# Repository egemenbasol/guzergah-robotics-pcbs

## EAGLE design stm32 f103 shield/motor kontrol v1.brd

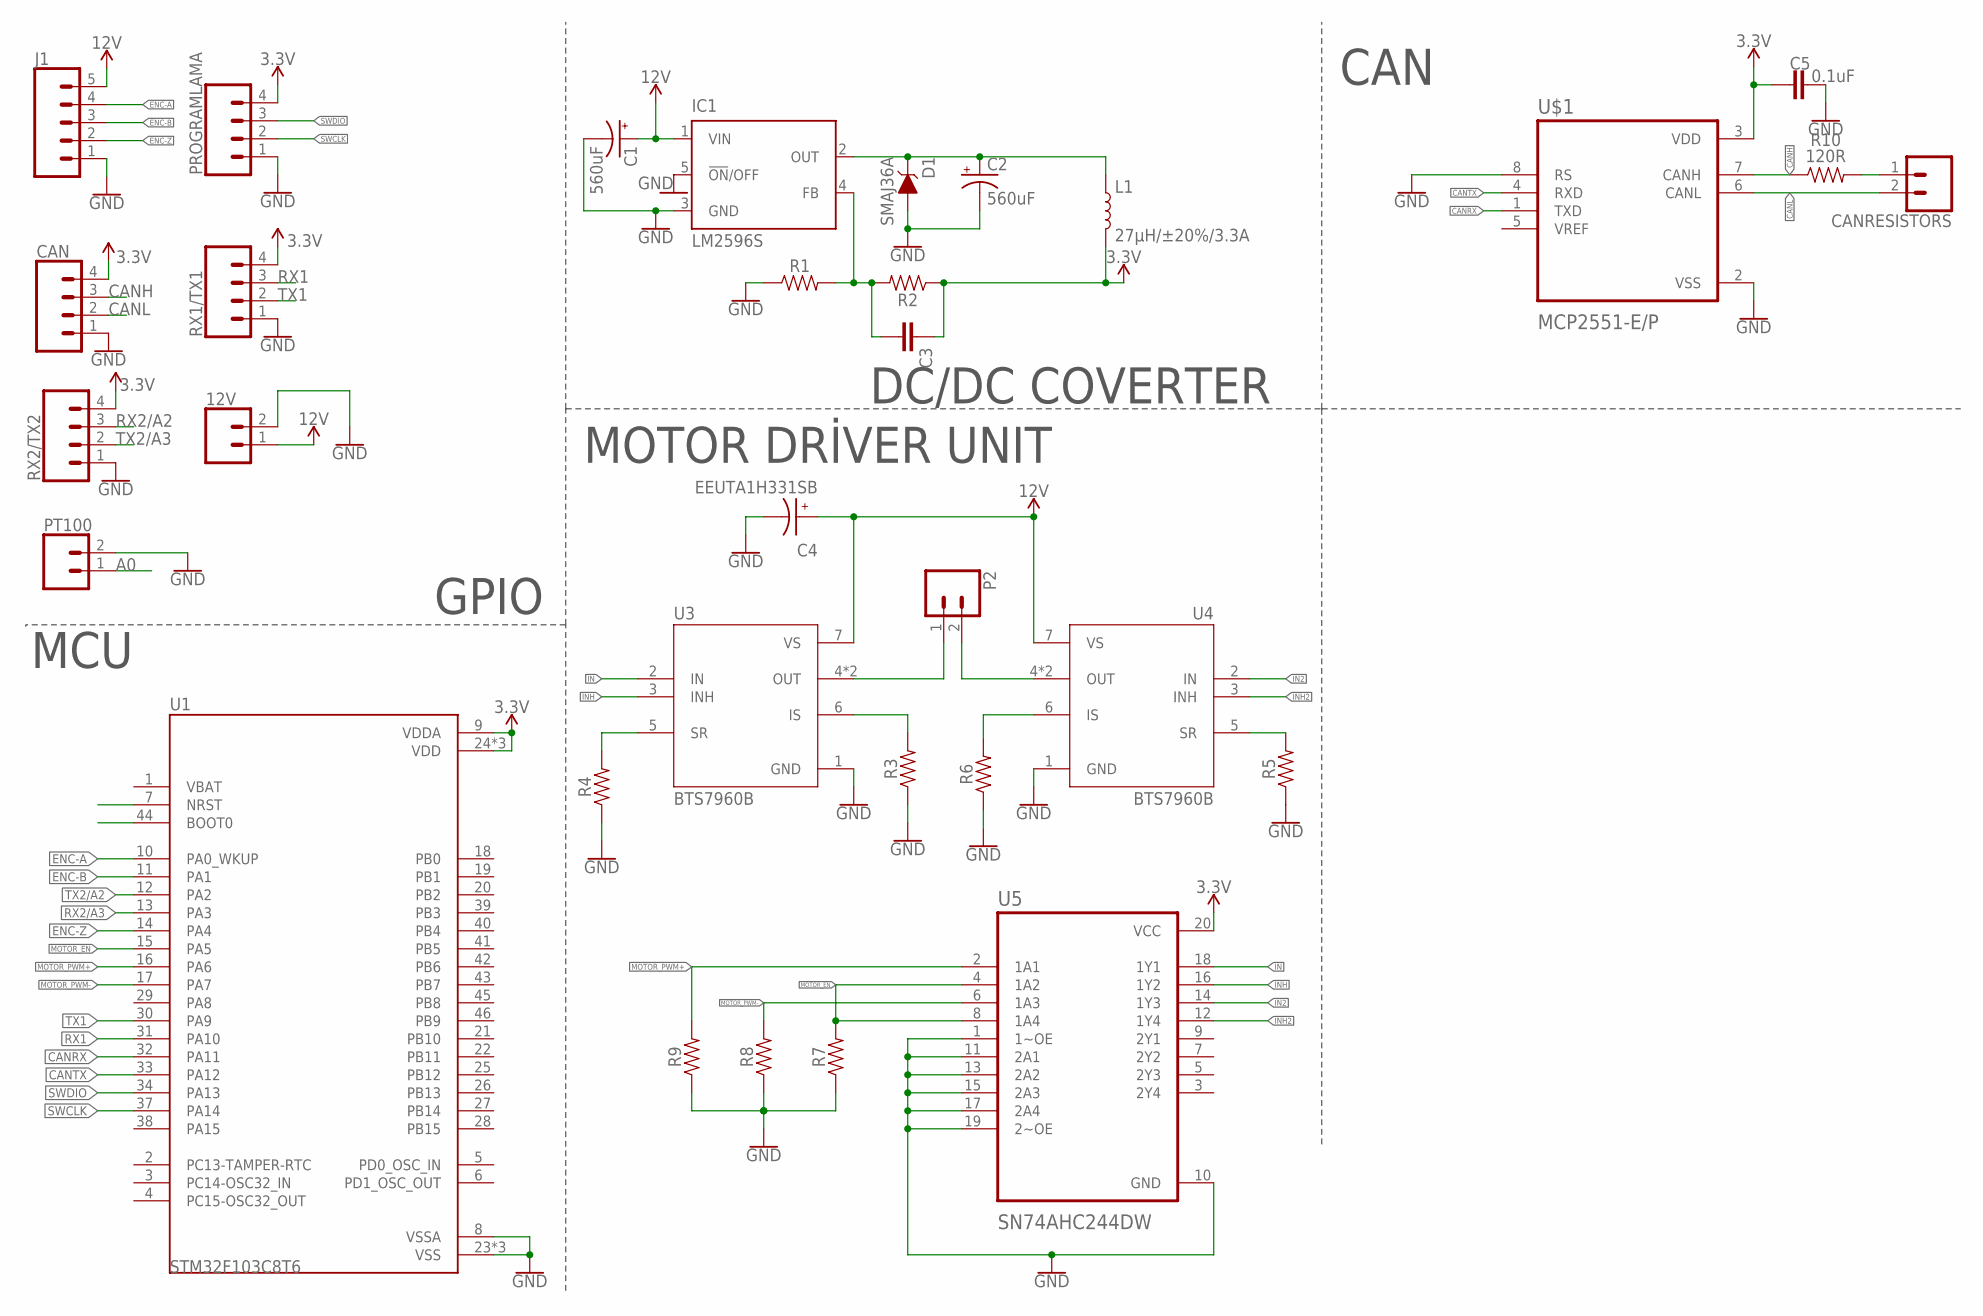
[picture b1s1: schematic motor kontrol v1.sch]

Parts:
12V: CONN_023.5MM_LOCK; SCREWTERMINAL-3.5MM-2_LOCK
C1, C2: 560uF; PANASONIC_G
C3: CAP-0805; 0805
C4: EEUTA1H331SB; CAPPRD750W80D1600H1500
C5: 0.1uF; 0805
CAN: CONN_04SCREW_LOCK; SCREWTERMINAL-3.5MM-4_LOCK
CANRESISTORS: CONN_02LOCK_LONGPADS; 1X02_LOCK_LONGPADS
D1: SMAJ36A; DO-214AC
IC1: LM2596S; TO263-5
J1: CONN_05SCREW; SCREWTERMINAL-3.5MM-5
L1: 27µH/±20%/3.3A; INDUCTOR_SDR1307
P2: CONN_023.5MM_LOCK; SCREWTERMINAL-3.5MM-2_LOCK
PROGRAMLAMA: CONN_04SCREW_LOCK; SCREWTERMINAL-3.5MM-4_LOCK
PT100: CONN_023.5MM_LOCK; SCREWTERMINAL-3.5MM-2_LOCK
R1, R2, R3, R4, R5, R6, R7, R8, R9: 0805
R10: 120R; 0805
RX1/TX1, RX2/TX2: CONN_04SCREW_LOCK; SCREWTERMINAL-3.5MM-4_LOCK
U1: STM32F103C8T6; QFP50P900X900X160-48N
U3, U4: BTS7960B; DPAK127P1490X440-8N
U5: SN74AHC244DW; SOIC127P1030X265-20N
U$1: MCP2551-E/P; DIP787W46P254L927H533Q8

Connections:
3.3V: C3.1, C5.2, CAN.4, L1.P$2 (2), PROGRAMLAMA.4, R2.1, RX1/TX1.4, RX2/TX2.4, U1.9 (VDDA), U1.24 (VDD), U1.36 (VDD), U1.48 (VDD), U5.20 (VCC), U$1.3 (VDD)
12V: 12V.1, C1.+, C4.P, IC1.1 (VIN), J1.5, U3.7 (VS), U4.7 (VS)
A0: PT100.1
CANH: CAN.3, R10.1, U$1.7 (CANH)
CANL: CAN.2, CANRESISTORS.2, U$1.6 (CANL)
CANRX: U1.32 (PA11), U$1.1 (TXD)
CANTX: U1.33 (PA12), U$1.4 (RXD)
ENC-A: J1.4, U1.10 (PA0_WKUP)
ENC-B: J1.3, U1.11 (PA1)
ENC-Z: J1.2, U1.14 (PA4)
GND: 12V.2, C1.-, C2.-, C4.N, C5.1, CAN.1, D1.A, IC1.3 (GND), IC1.5 (!ON!/OFF), J1.1, PROGRAMLAMA.1, PT100.2, R1.1, R3.1, R4.1, R5.1, R6.1, R7.1, R8.1, R9.1, RX1/TX1.1, RX2/TX2.1, U1.8 (VSSA), U1.23 (VSS), U1.35 (VSS), U1.47 (VSS), U3.1 (GND), U4.1 (GND), U5.1 (1~OE), U5.10 (GND), U5.11 (2A1), U5.13 (2A2), U5.15 (2A3), U5.17 (2A4), U5.19 (2~OE), U$1.2 (VSS), U$1.8 (RS)
IN: U3.2 (IN), U5.18 (1Y1)
IN2: U4.2 (IN), U5.14 (1Y3)
INH: U3.3 (INH), U5.16 (1Y2)
INH2: U4.3 (INH), U5.12 (1Y4)
MOTOR_EN: R7.2, U1.15 (PA5), U5.4 (1A2), U5.8 (1A4)
MOTOR_PWM+: R9.2, U1.16 (PA6), U5.2 (1A1)
MOTOR_PWM-: R8.2, U1.17 (PA7), U5.6 (1A3)
unnamed: C2.+, D1.C, IC1.2 (OUT), L1.P$1 (1)
unnamed: C3.2, IC1.4 (FB), R1.2, R2.2
unnamed: P2.1, U3.4 (OUT), U3.8 (OUT)
unnamed: P2.2, U4.4 (OUT), U4.8 (OUT)
unnamed: CANRESISTORS.1, R10.2
unnamed: R5.2, U4.5 (SR)
unnamed: R6.2, U4.6 (IS)
unnamed: R3.2, U3.6 (IS)
unnamed: R4.2, U3.5 (SR)
RX1: RX1/TX1.3, U1.31 (PA10)
RX2/A2: RX2/TX2.3
RX2/A3: U1.13 (PA3)
SWCLK: PROGRAMLAMA.2, U1.37 (PA14)
SWDIO: PROGRAMLAMA.3, U1.34 (PA13)
TX1: RX1/TX1.2, U1.30 (PA9)
TX2/A2: U1.12 (PA2)
TX2/A3: RX2/TX2.2

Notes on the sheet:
MCU
CAN
DC/DC COVERTER
GPIO
MOTOR DRİVER UNIT

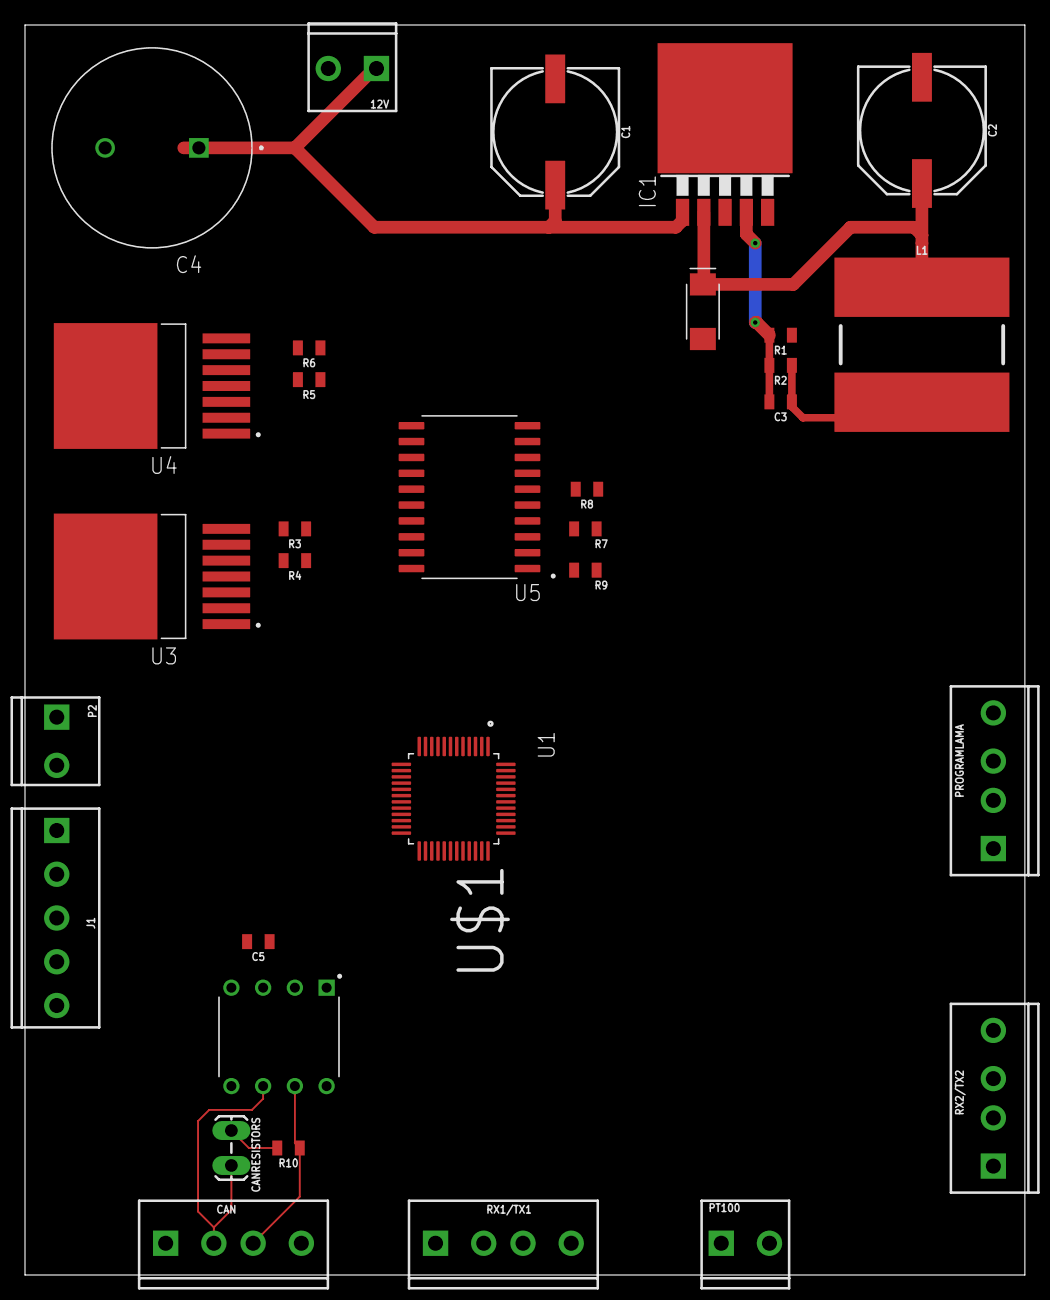
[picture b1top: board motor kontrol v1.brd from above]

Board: 2 copper layers, 80.0 x 100.0 mm, 32 parts (0 on the bottom side), 30 nets.

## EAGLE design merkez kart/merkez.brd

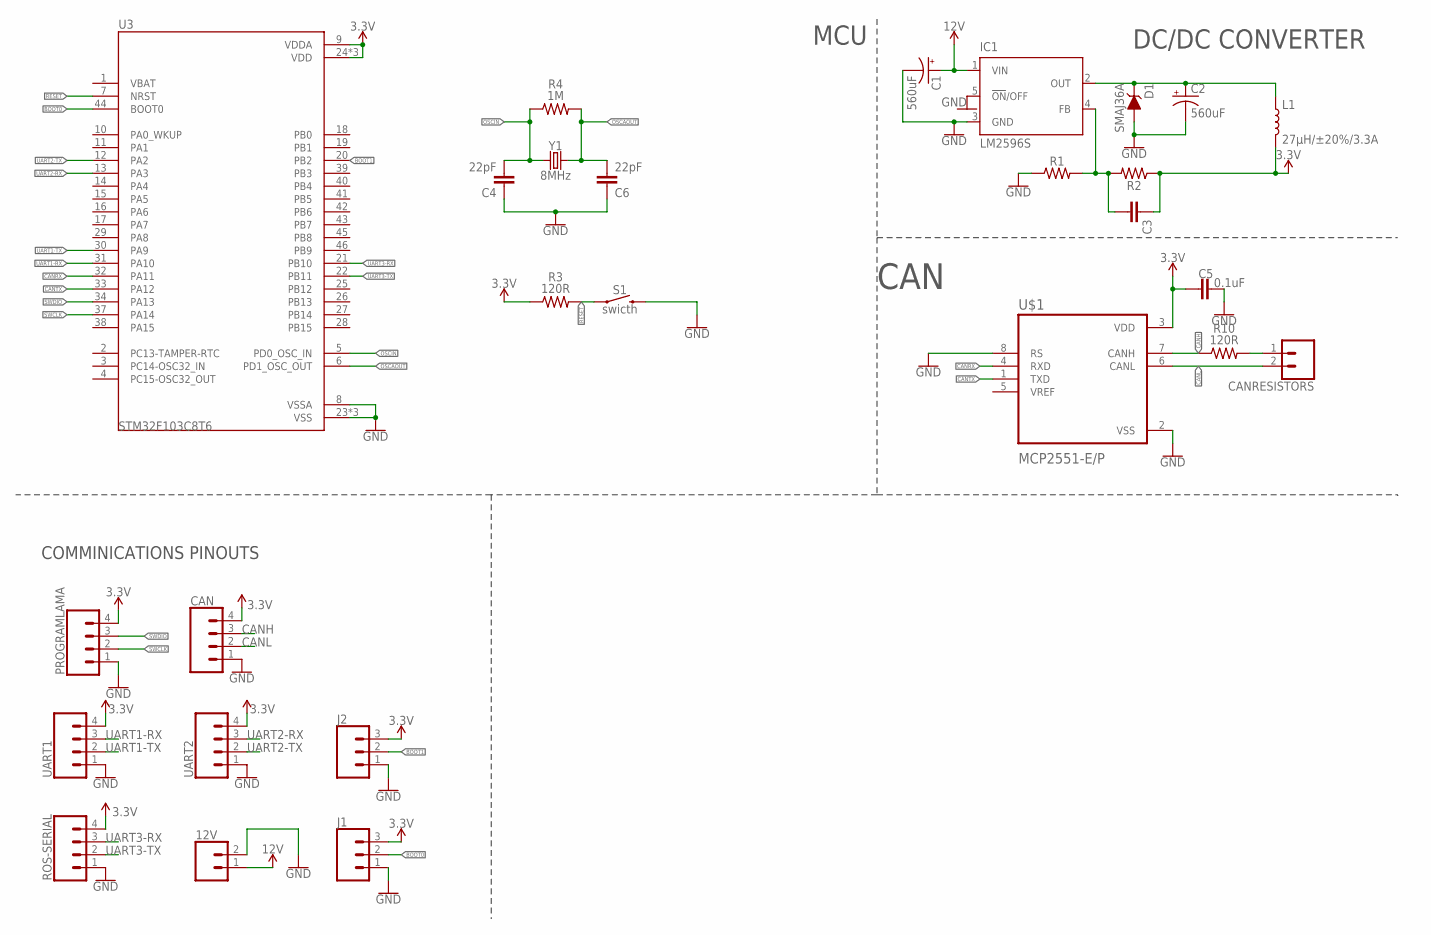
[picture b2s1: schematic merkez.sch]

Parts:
12V: CONN_023.5MM_LOCK; SCREWTERMINAL-3.5MM-2_LOCK
C1, C2: 560uF; PANASONIC_G
C3: CAP-0805; 0805
C4, C6: 22pF; 0805
C5: 0.1uF; 0805
CAN: CONN_04SCREW_LOCK; SCREWTERMINAL-3.5MM-4_LOCK
CANRESISTORS: CONN_02LOCK_LONGPADS; 1X02_LOCK_LONGPADS
D1: SMAJ36A; DO-214AC
IC1: LM2596S; TO263-5
J1, J2: 455-1750-1-ND; 1X03
L1: 27µH/±20%/3.3A; INDUCTOR_SDR1307
PROGRAMLAMA: CONN_04SCREW_LOCK; SCREWTERMINAL-3.5MM-4_LOCK
R1, R2: 0805
R3, R10: 120R; 0805
R4: 1M; 0805
ROS-SERIAL: CONN_04SCREW_LOCK; SCREWTERMINAL-3.5MM-4_LOCK
S1: swicth; TACTILE_SWITCH_SMD_5.2MM
U3: STM32F103C8T6; QFP50P900X900X160-48N
U$1: MCP2551-E/P; DIP787W46P254L927H533Q8
UART1, UART2: CONN_04SCREW_LOCK; SCREWTERMINAL-3.5MM-4_LOCK
Y1: 8MHz; HC49UP

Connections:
3.3V: C3.1, C5.2, CAN.4, J1.3, J2.3, L1.P$2 (2), PROGRAMLAMA.4, R2.1, R3.1, ROS-SERIAL.4, U3.9 (VDDA), U3.24 (VDD), U3.36 (VDD), U3.48 (VDD), U$1.3 (VDD), UART1.4, UART2.4
12V: 12V.1, C1.+, IC1.1 (VIN)
BOOT0: J1.2, U3.44 (BOOT0)
BOOT1: J2.2
CANH: CAN.3, R10.1, U$1.7 (CANH)
CANL: CAN.2, CANRESISTORS.2, U$1.6 (CANL)
CANRX: U3.32 (PA11), U$1.4 (RXD)
CANTX: U3.33 (PA12), U$1.1 (TXD)
GND: 12V.2, C1.-, C2.-, C4.1, C5.1, C6.1, CAN.1, D1.A, IC1.3 (GND), IC1.5 (!ON!/OFF), J1.1, J2.1, PROGRAMLAMA.1, R1.1, ROS-SERIAL.1, S1.3 (2), U3.8 (VSSA), U3.23 (VSS), U3.35 (VSS), U3.47 (VSS), U$1.2 (VSS), U$1.8 (RS), UART1.1, UART2.1
unnamed: C2.+, D1.C, IC1.2 (OUT), L1.P$1 (1)
unnamed: C3.2, IC1.4 (FB), R1.2, R2.2
unnamed: CANRESISTORS.1, R10.2
OSCAOUT: C6.2, R4.2, U3.6 (PD1_OSC_OUT), Y1.2
OSCIN: C4.2, R4.1, U3.5 (PD0_OSC_IN), Y1.1
RESET: R3.2, S1.1, U3.7 (NRST)
SWCLK: PROGRAMLAMA.2, U3.37 (PA14)
SWDIO: PROGRAMLAMA.3, U3.34 (PA13)
UART1-RX: U3.31 (PA10), UART1.3
UART1-TX: U3.30 (PA9), UART1.2
UART2-RX: U3.13 (PA3), UART2.3
UART2-TX: U3.12 (PA2), UART2.2
UART3-RX: ROS-SERIAL.3, U3.21 (PB10)
UART3-TX: ROS-SERIAL.2, U3.22 (PB11)

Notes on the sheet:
CAN
DC/DC CONVERTER
MCU
COMMINICATIONS PINOUTS

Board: 2 copper layers, 27 parts (0 on the bottom side), 22 nets, no tracks yet.

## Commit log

2023-01-26 Merkez kart dosyaları yüklendi
2023-01-26 Motor kontrol kartı yüklendi

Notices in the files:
parts and their libraries:
SparkFun-Connectors: Licensing: Creative Commons ShareAlike 4.0 International - https://creativecommons.org/licenses/by-sa/4.0
